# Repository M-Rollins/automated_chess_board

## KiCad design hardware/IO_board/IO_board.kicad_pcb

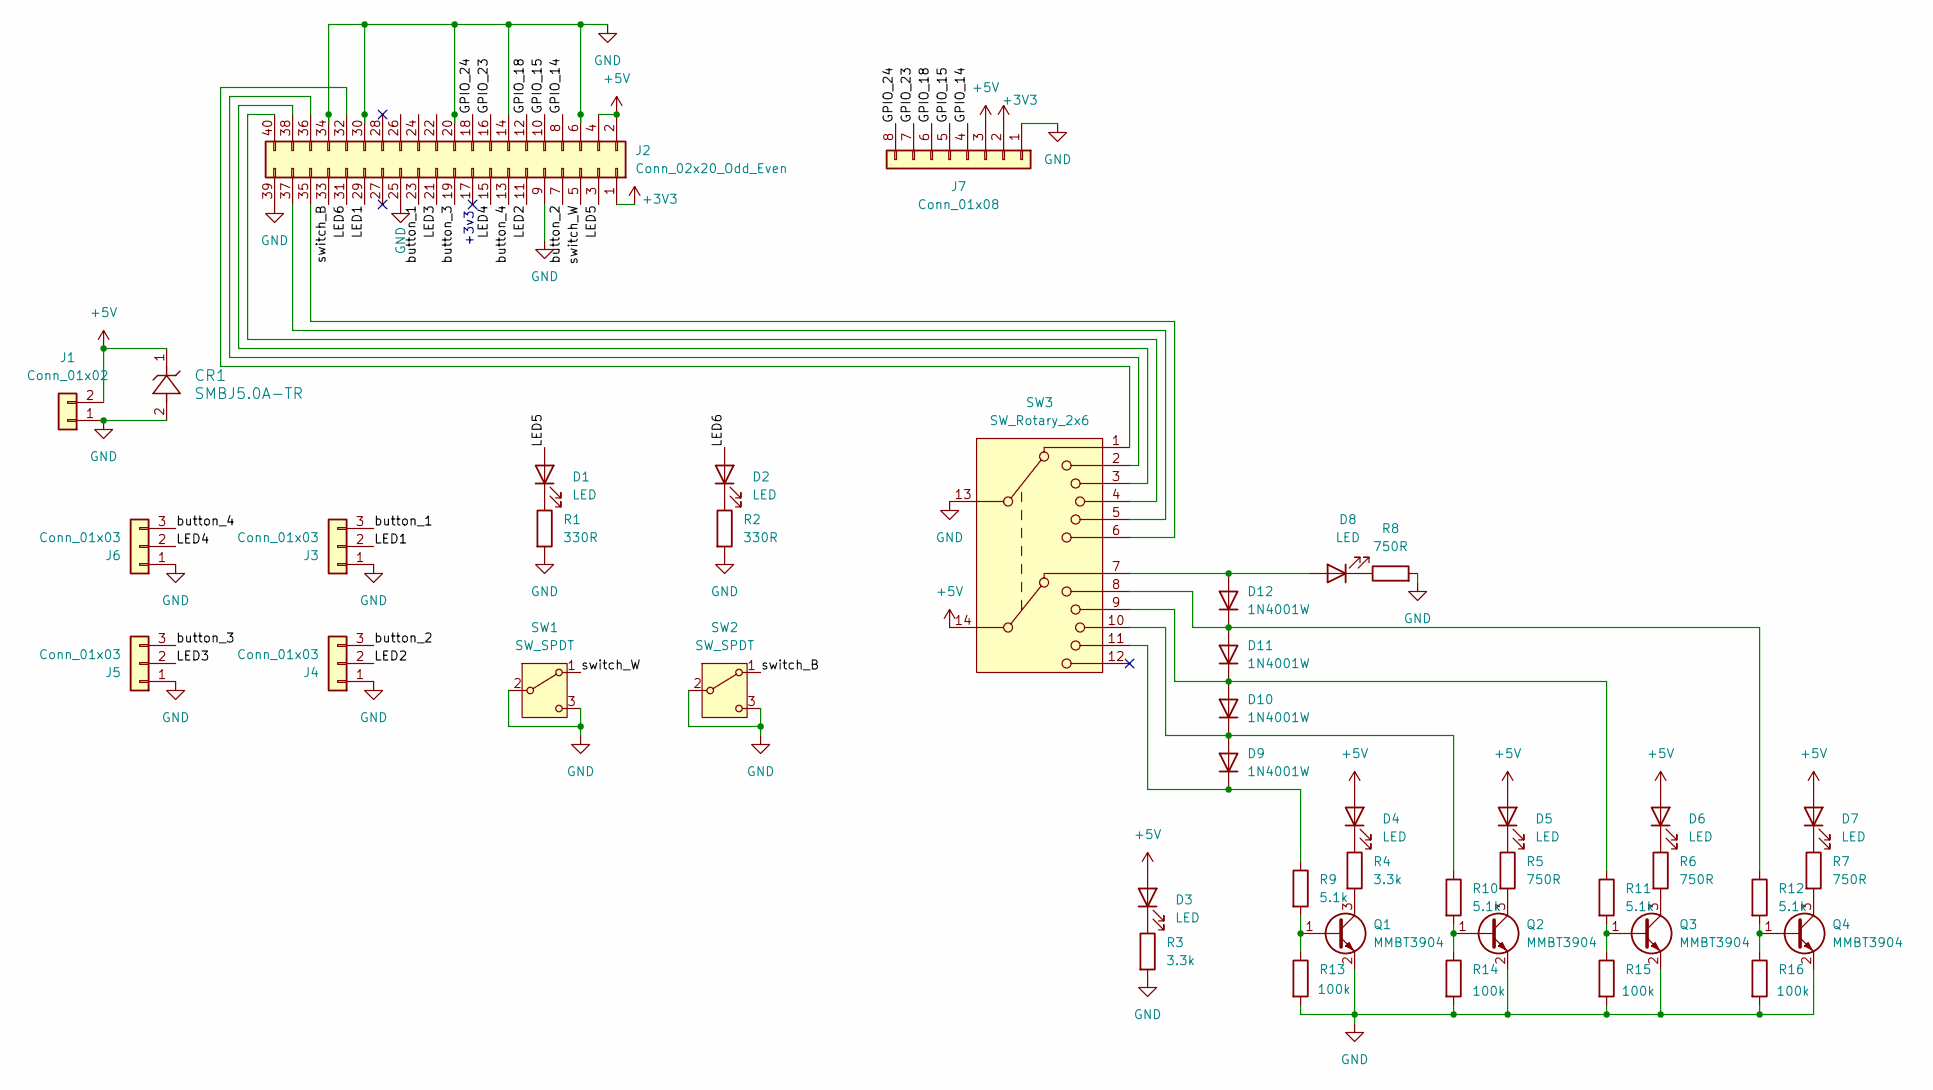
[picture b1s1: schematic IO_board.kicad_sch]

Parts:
CR1: SMBJ5.0A-TR; SMB_STM
D1, D2: LED; LED_D5.0mm
D3, D4, D5, D6, D7, D8: LED; LED_0805_2012Metric_Pad1.15x1.40mm_HandSolder
D9, D10, D11, D12: 1N4001W; D_SOD-123F
J1: Conn_01x02; JST_EH_B2B-EH-A_1x02_P2.50mm_Vertical
J2: Conn_02x20_Odd_Even; PinHeader_2x20_P2.54mm_Vertical_MIRROR
J3, J4, J5, J6: Conn_01x03; JST_EH_B3B-EH-A_1x03_P2.50mm_Vertical
J7: Conn_01x08; PinHeader_1x08_P2.54mm_Vertical
Q1, Q2, Q3, Q4: MMBT3904; SOT-23
R1, R2: 330R; R_0805_2012Metric_Pad1.20x1.40mm_HandSolder
R3, R4: 3.3k; R_0805_2012Metric_Pad1.20x1.40mm_HandSolder
R5, R6, R7, R8: 750R; R_0805_2012Metric_Pad1.20x1.40mm_HandSolder
R9, R10, R11, R12: 5.1k; R_0805_2012Metric_Pad1.20x1.40mm_HandSolder
R13, R14, R15, R16: 100k; R_0805_2012Metric_Pad1.20x1.40mm_HandSolder
SW1, SW2: SW_SPDT; SW_toggle
SW3: SW_Rotary_2x6; SW_rotary_2x6

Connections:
+3V3: J2.1, J7.2
+5V: CR1.1, D3.2 (A), D4.2 (A), D5.2 (A), D6.2 (A), D7.2 (A), J1.2, J2.2, J2.4, J7.3, SW3.14
/GPIO_14: J2.8, J7.4
/GPIO_15: J2.10, J7.5
/GPIO_18: J2.12, J7.6
/GPIO_23: J2.16, J7.7
/GPIO_24: J2.18, J7.8
/LED1: J2.29, J3.2
/LED2: J2.11, J4.2
/LED3: J2.21, J5.2
/LED4: J2.15, J6.2
/LED5: D1.2 (A), J2.3
/LED6: D2.2 (A), J2.31
/button_1: J2.23, J3.3
/button_2: J2.7, J4.3
/button_3: J2.19, J5.3
/button_4: J2.13, J6.3
/switch_B: J2.33, SW2.1 (A)
/switch_W: J2.5, SW1.1 (A)
GND: CR1.2, J1.1, J2.6, J2.9, J2.14, J2.20, J2.25, J2.30, J2.34, J2.39, J3.1, J4.1, J5.1, J6.1, J7.1, Q1.2 (E), Q2.2 (E), Q3.2 (E), Q4.2 (E), R1.2, R2.2, R3.2, R8.2, R13.2, R14.2, R15.2, R16.2, SW1.2 (B), SW1.3 (C), SW2.2 (B), SW2.3 (C), SW3.13
unnamed: D1.1 (K), R1.1
unnamed: D2.1 (K), R2.1
unnamed: D3.1 (K), R3.1
unnamed: D4.1 (K), R4.1
unnamed: D5.1 (K), R5.1
unnamed: D6.1 (K), R6.1
unnamed: D7.1 (K), R7.1
unnamed: D8.1 (K), R8.1
unnamed: D9.1 (K), R9.1, SW3.11
unnamed: D10.2 (A), D11.1 (K), R11.1, SW3.9
unnamed: D9.2 (A), D10.1 (K), R10.1, SW3.10
unnamed: D11.2 (A), D12.1 (K), R12.1, SW3.8
unnamed: D8.2 (A), D12.2 (A), SW3.7
unnamed: J2.32, SW3.1
unnamed: J2.35, SW3.6
unnamed: J2.36, SW3.2
unnamed: J2.37, SW3.5
unnamed: J2.38, SW3.3
unnamed: J2.40, SW3.4
unnamed: Q1.1 (B), R9.2, R13.1
unnamed: Q1.3 (C), R4.2
unnamed: Q2.1 (B), R10.2, R14.1
unnamed: Q2.3 (C), R5.2
unnamed: Q3.1 (B), R11.2, R15.1
unnamed: Q3.3 (C), R6.2
unnamed: Q4.1 (B), R12.2, R16.1
unnamed: Q4.3 (C), R7.2

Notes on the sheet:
+3v3

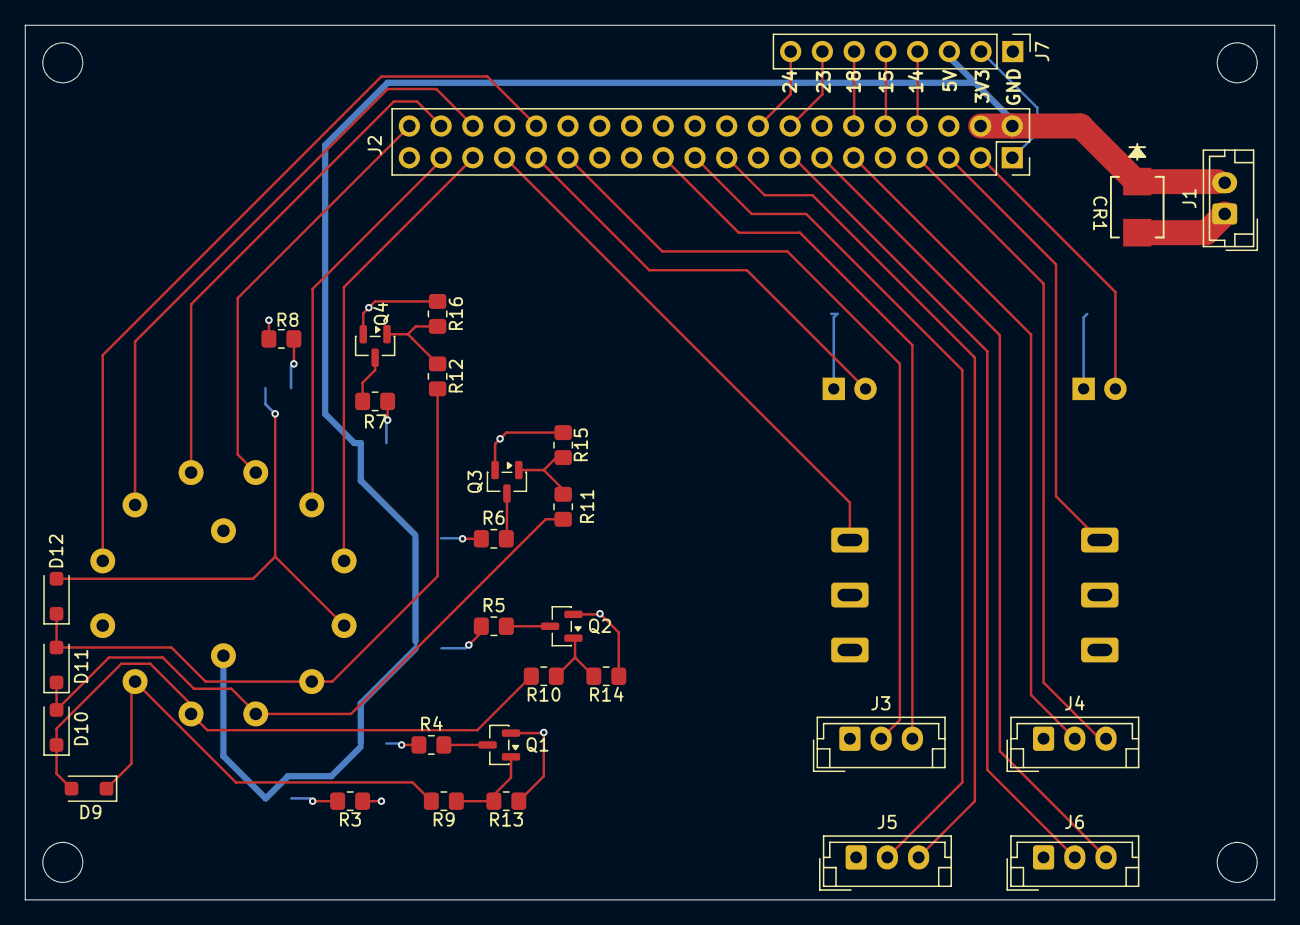
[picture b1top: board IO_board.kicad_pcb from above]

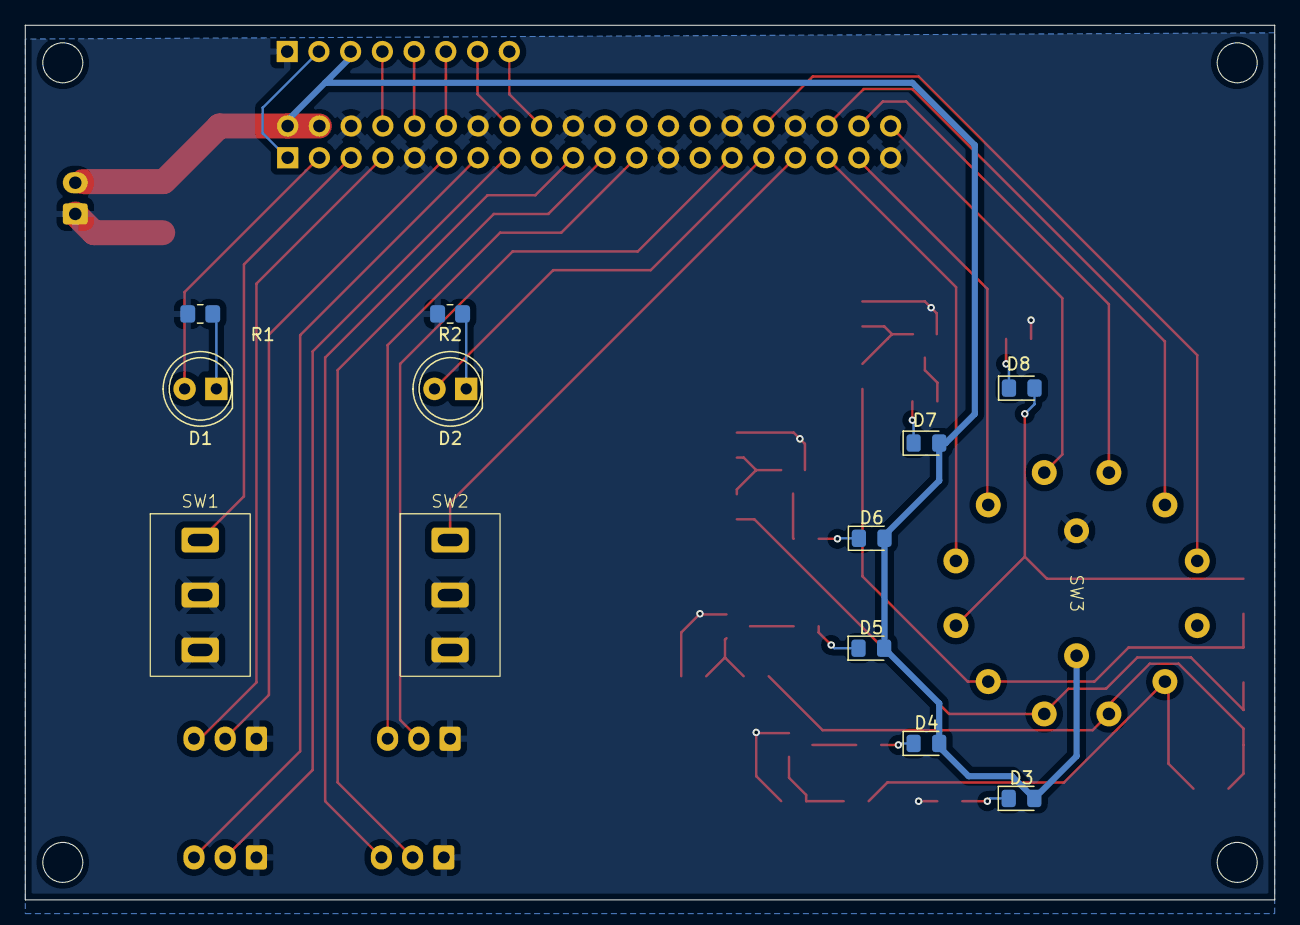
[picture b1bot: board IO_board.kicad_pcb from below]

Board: 2 copper layers, 100.0 x 70.0 mm, 43 parts (13 on the bottom side), 47 nets.

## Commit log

2025-01-15 added stockfish
2025-01-19 commit test
2025-01-19 adjustded board dimensions
2025-06-28 added reference for board commands
2025-06-28 began implementing basic acceleration (x only)
2025-06-29 Broke motion control into separate library
    MotorControl library contains StepperMotor class plus new Axis class which stores current and target position for one motor and controls motion
2025-06-29 implemented microstepping
2025-08-18 command handling and board tracking updates
    - Modified command parsing
    - began implementing board state tracking and board-aware path planning for piece movement
2025-08-20 Implemented board-aware movement (no captures) (untested)
    - Instead of moving pieces directly from starting to ending squares, the program tracks the board state and attempts to find the shortest path that does not cross any occupied squares.
    - Added a command to print out the board state
    * captures are not yet implemented. Attempting a move where the destination square is occupied will result in failure to find a valid path.
    * Code compiles, but changed have not been tested on the board
2025-10-04 Movement bug fixing
2025-10-04 Saved drivers that work with arduino
2025-10-04 reversed order of ranks in board representation
2025-10-05 Added command to play moves using algebraic notation
    -some bugs with path finding / capture logic (ranks and files flipped somewhere?)
2025-10-19 Path finding updates
    -Fixed path finding logic errors
    -Added function to realign pieces
    -Minor refactoring
    -Notes:
    -close to memory limit, may cause issues
    -serial input buffer is 64 bytes: transmitting longer strings at a time causes problems
2025-10-19 Implemented board setup command and board dimension query, used F() wrapper for string literals to save dynamic memory
2025-11-16 experiments with pyserial library for USB communication
2025-11-16 Create engine_test.py
    Script for testing pychess SimpleEngine
    Note: the engine does not work in Spyder's IPython console (some kind of asyncio conflict). Needs to be run in an external terminal
2025-11-16 Began integrating physical board control with python script
    Upon running main.py, the computer connects to the microcontroller (running BoardControl.ino). The user can start a game with both, one, or neither side controlled by stockfish. During the game, move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
2025-11-16 added functionality to computer-side code
    -added handling of castling
    -added commands to initalize/setup board, home axes, adjust pieces
    -added ability to quit and then resume a game
2025-11-16 formatting
2025-11-19 Updated pathing
    Path finding updates:
    -Use Djikstra's algorithm to find shortest path
    -Include knight's moves (e.g. (+1, +2))
    -Penalty for changing direction
    -Penalty for making diagonal moves next to pieces
    -When x and y need to move different distances, scale speeds so they move in a straight line and arrive at the same time
2025-11-23 Create motion_alg_test.py
    Python script for testing and visualizing new motion planning algorithms. Goal is to implement smooth paths that don't come to rest at turns.
2025-11-30 Implemented smooth path following
    Instead of stopping at each direction change, the tool takes a path that passes through the points with smooth velocities.
2025-12-19 Uploaded IO PCB design files
2025-12-19 Added ability to change engine skill level
2026-04-11 Frist attempt at using IO board for control
2026-04-11 updated engine and GPIO tests
2026-04-12 IO bug fixes
2026-04-15 Updated main loop and keyboard input logic
2026-05-03 Implemented game control with IO harware
2026-05-03 Soft LED blinking
2026-06-12 minor fixes
